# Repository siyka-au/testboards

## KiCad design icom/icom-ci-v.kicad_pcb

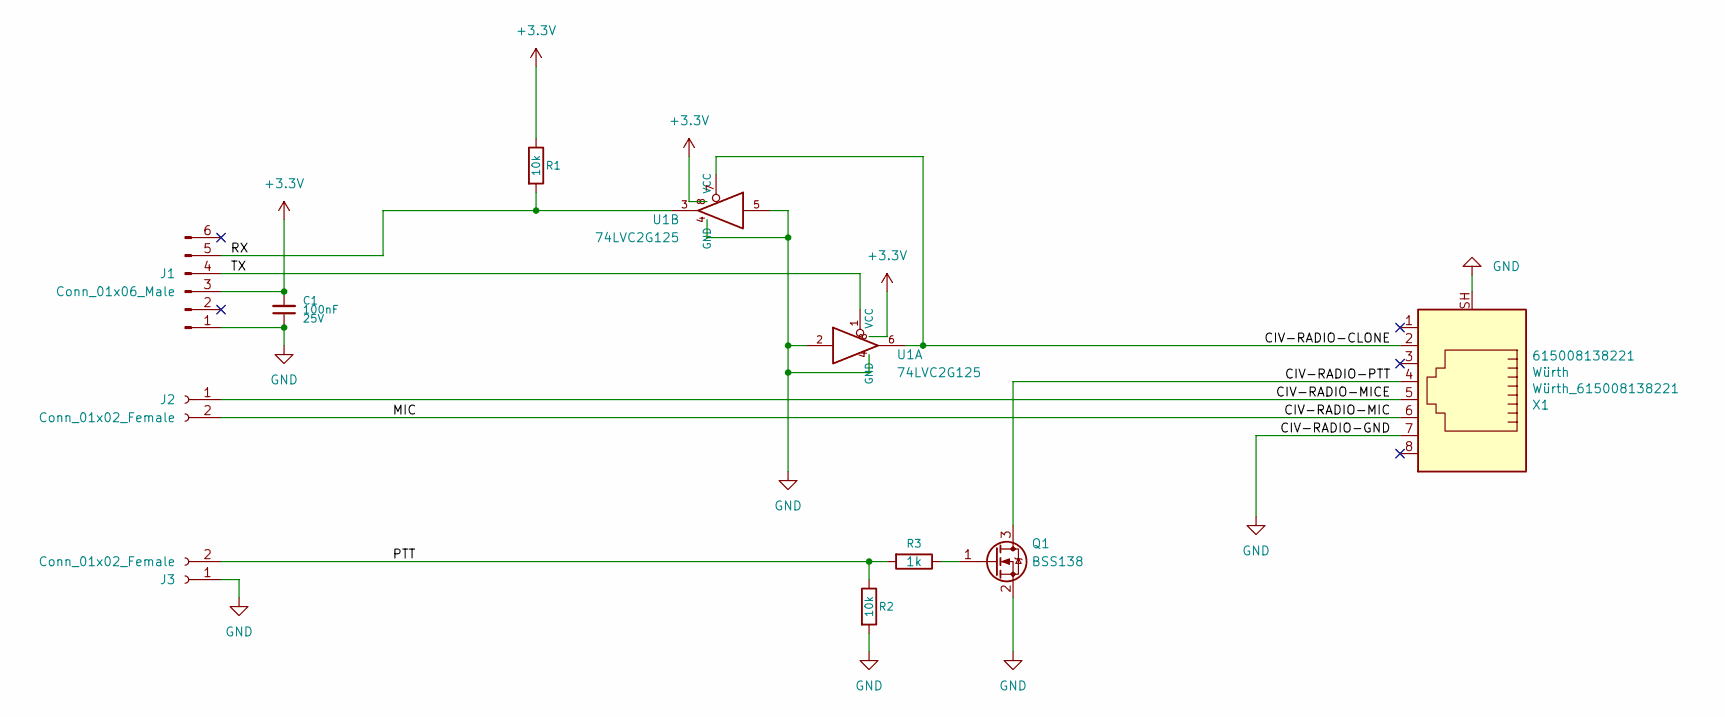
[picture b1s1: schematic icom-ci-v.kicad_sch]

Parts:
C1: 100nF; C_0603_1608Metric; Voltage 25V
J1: Conn_01x06_Male; PinHeader_1x06_P2.54mm_Vertical
J2, J3: Conn_01x02_Female; PhoenixContact_MCV_1,5_2-G-3.5_1x02_P3.50mm_Vertical
Q1: BSS138; SOT-23
R1, R2: 10k; R_0603_1608Metric; Tolerance 1%
R3: 1k; R_0603_1608Metric; Tolerance 1%
U1: 74LVC2G125; TSSOP-8_3x3mm_P0.65mm
X1: Würth_615008138221; RJ45_Wuerth_615008138221_Vertical; Manufacturer Part Number 615008138221

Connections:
+3.3V: C1.2, J1.3, R1.1, U1.8 (VCC)
/CIV-RADIO-CLONE: U1.6, U1.7, X1.2
/CIV-RADIO-MIC: J2.2, X1.6
/CIV-RADIO-MICE: J2.1, X1.5
/CIV-RADIO-PTT: Q1.3 (D), X1.4
/PTT: J3.2, R2.1, R3.2
/RX: J1.5, R1.2, U1.3
/TX: J1.4, U1.1
GND: C1.1, J1.1, J3.1, Q1.2 (S), R2.2, U1.2, U1.4 (GND), U1.5, X1.7, X1.SH
unnamed: Q1.1 (G), R3.1

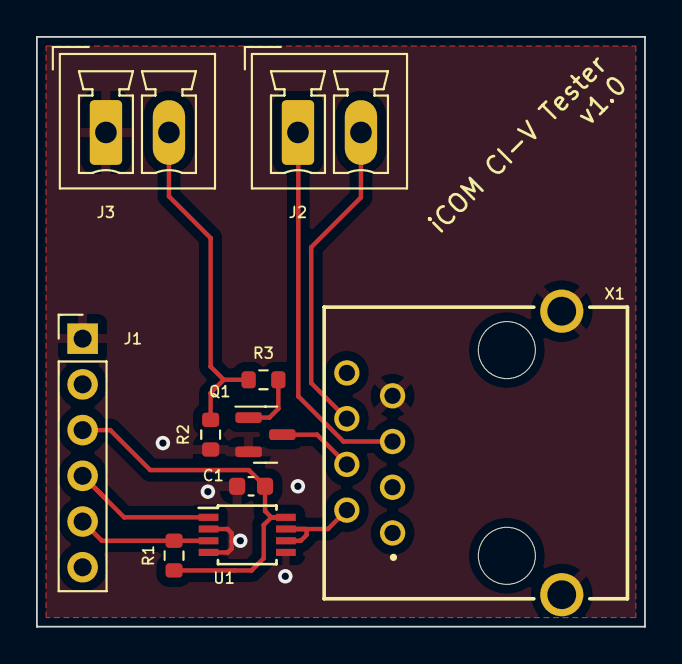
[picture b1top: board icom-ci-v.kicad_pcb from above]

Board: 2 copper layers, 33.8 x 32.8 mm, 10 parts (0 on the bottom side), 10 nets.

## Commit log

2022-08-11 Added gitignore
2022-08-11 Deleted backups
2022-08-12 PCB: cleanups
2022-08-12 BOM: add interactive BOM
2022-08-12 Moved J1 and J2 to give clearance for the plug against the RJ45 connector
